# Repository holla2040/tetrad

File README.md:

# hexad
A 4-axis ESP32 GRBL board 

Board
    
    [Schematic](board/hexad-sch.pdf)

Requires
    [ESP32SSDP](https://github.com/luc-github/ESP32SSDP)

Compiling
    Select Board "ESP32 Dev Module"
    Flash Size "4MB (32Mb)"
    Partition Scheme "Minimal SPIFFS (1.9MB APP with OTA/190kB SPIFFS)"

    set options, like N_AXIS in config.h

----

Based on Dring's ESP32 GRBL port
 * [Grbl_ESP32 Development Board Version 3.1](http://www.buildlog.net/blog/2018/11/grbl_esp32-development-board-version-3-1/) 
 * [Source](https://github.com/bdring/Grbl_Esp32)
 * [Schematic](http://www.buildlog.net/blog/wp-content/uploads/2018/10/schm_esp32_cnc_test_v3p1.pdf)
 * [Wiki](https://github.com/bdring/Grbl_Esp32/wiki)

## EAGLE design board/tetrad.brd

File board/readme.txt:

This information, board files, assembly instructions and bill of
materials are company confidental.
Not for distribution.

board
    hexad

version
    v1.0

date
    191101

fudicials at
    x,y
    x,y

2 layer description
    2 layer board
        crc component cream
        plc component side silkscreen
        stc component side solder stop mask
        cmp component side copper
        sol solder side copper
        sts solder side solder stop mask
        pls solder side silkscreen
        crs solder cream

        drd drill data
        dri drill info
        gpi gerber info

2 layer stack up sequence
    top     x.cmp
    bottom  x.sol

contact info
    Craig Hollabaugh
    970 690 4911
    craig@hollabaugh.com

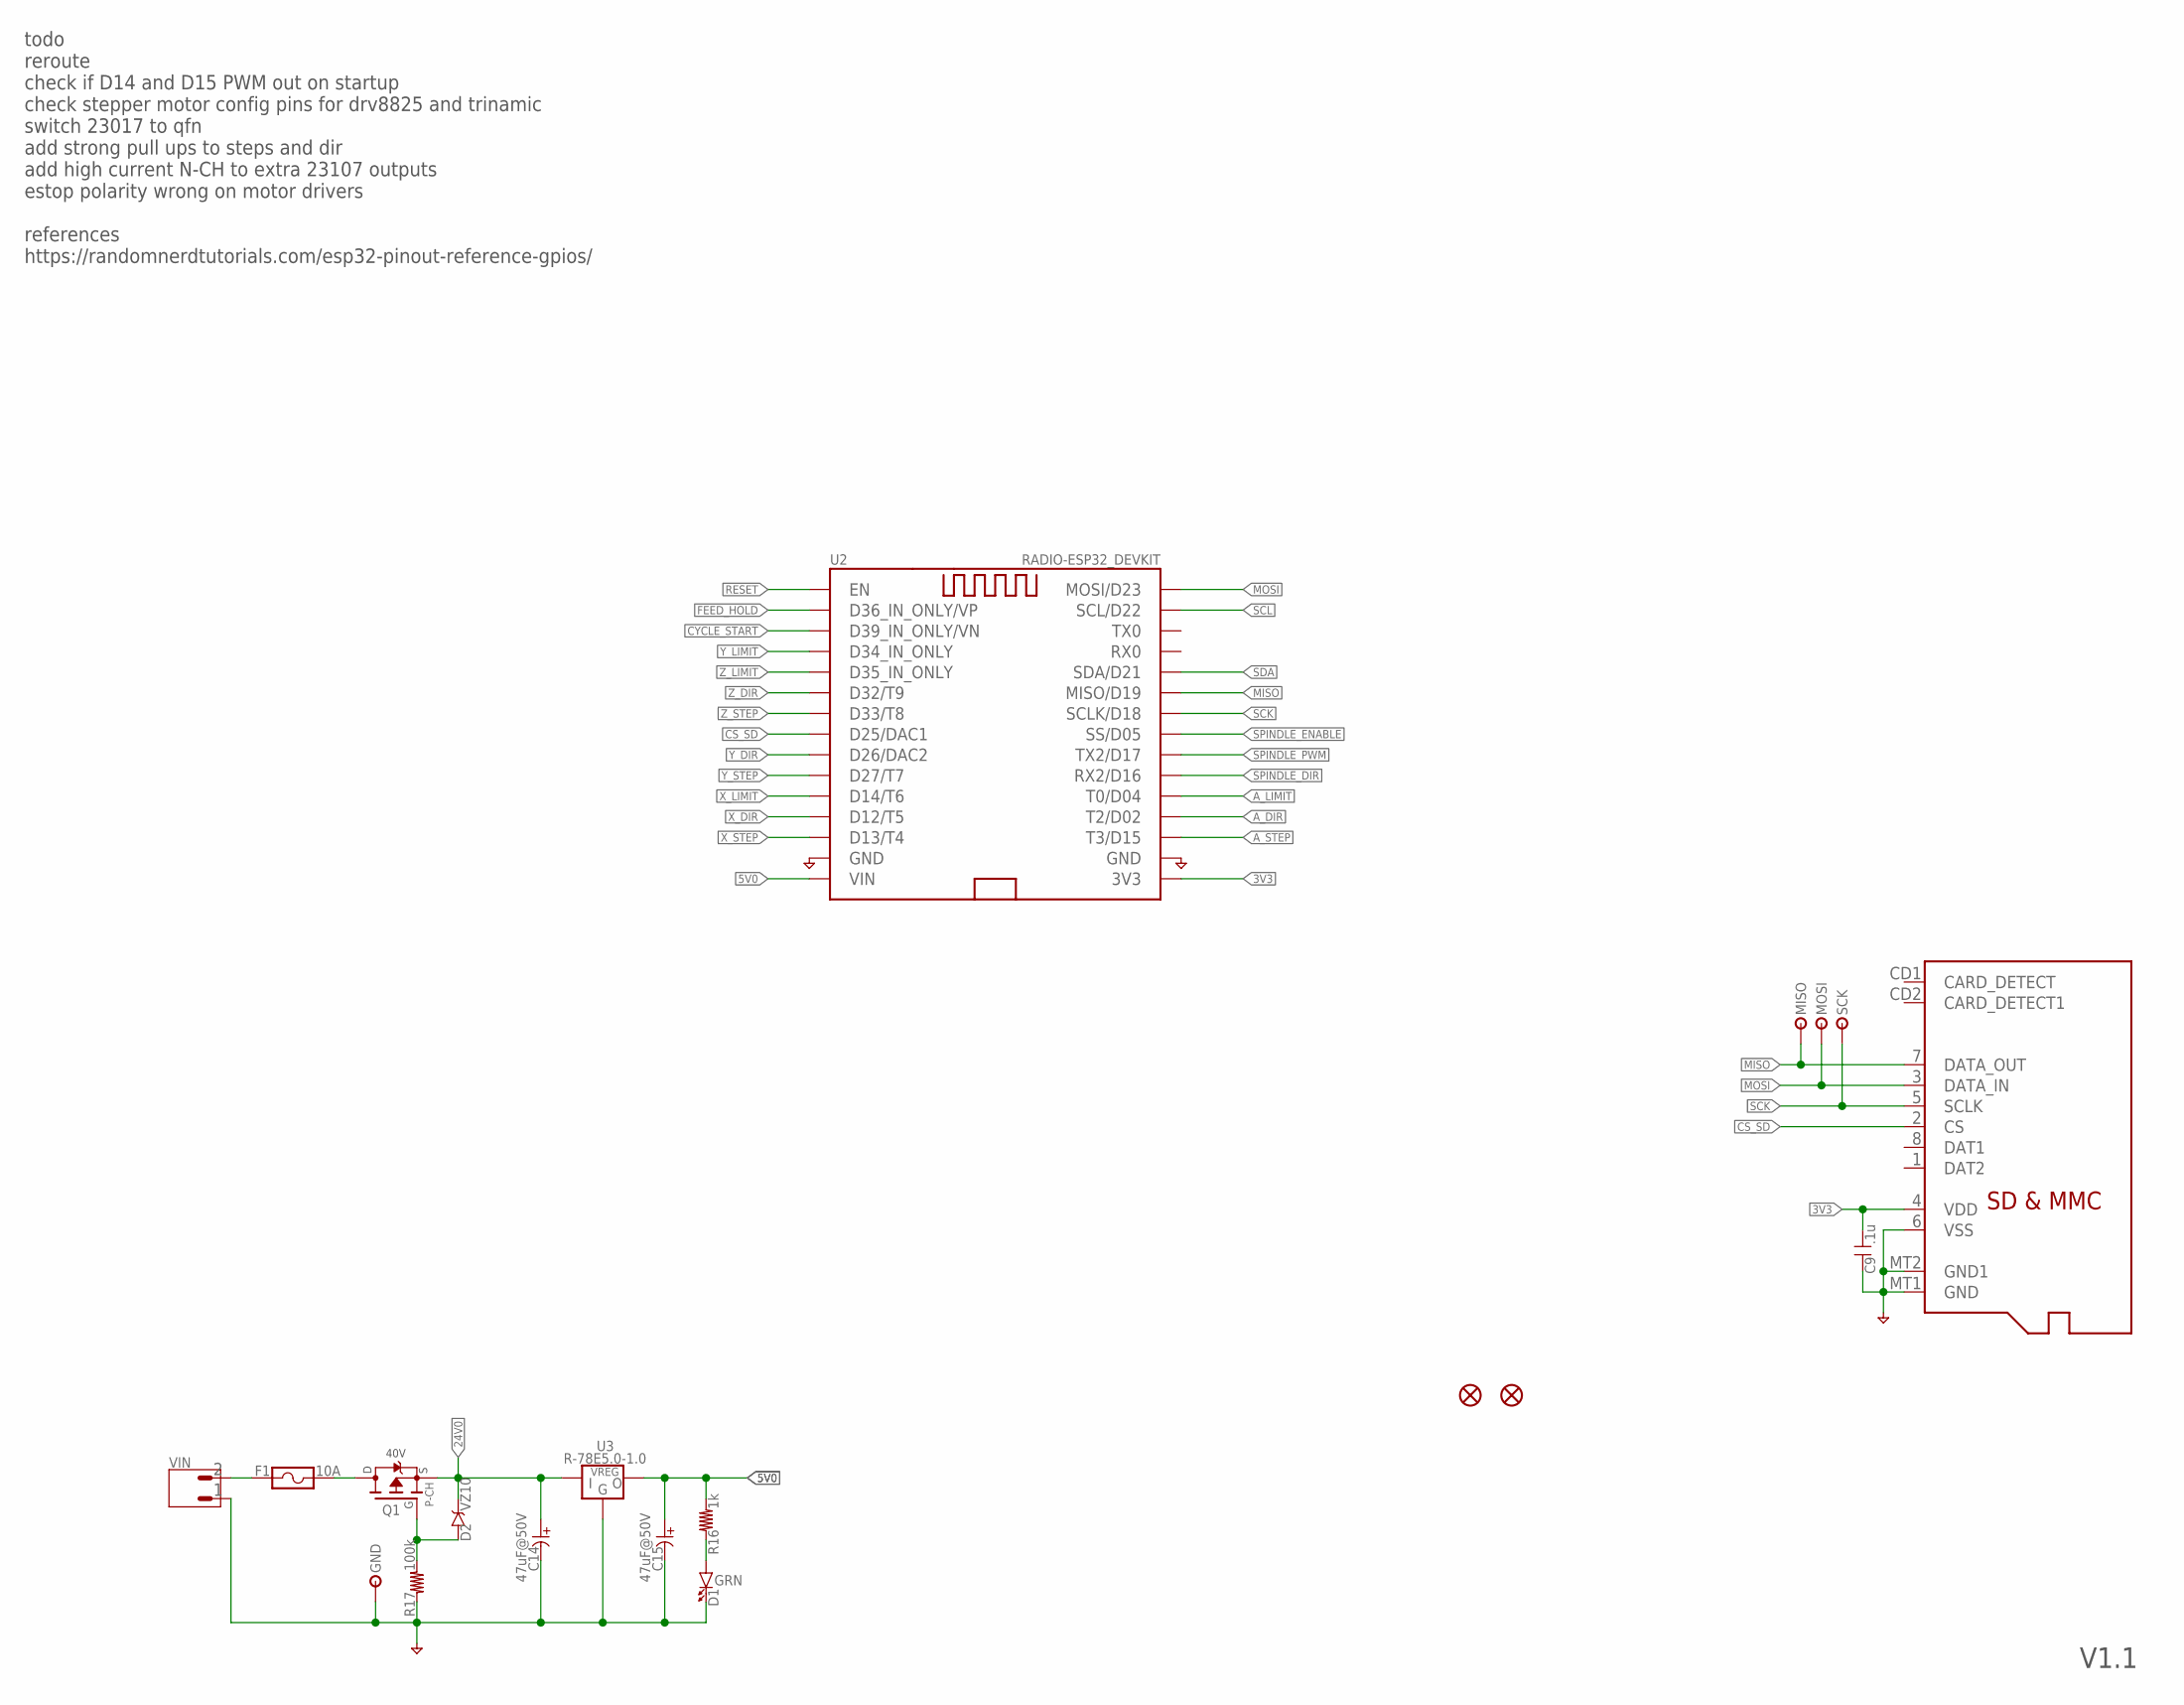
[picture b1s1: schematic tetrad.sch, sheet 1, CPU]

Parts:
C9: .1u; C-0603
C14, C15: 47uF@50V; C-E-6
D1: GRN; LED-0603
D2: VZ10; D-SOD323
F1: 10A; 3557-2
FID1, FID2: FIDUCIAL-MICRO
GND: TESTPOINTTHRU; TPTHRU
J1: CONN-MICROSD-2908-05WB-MG
MISO: TESTPOINTTHRU; TPTHRU
MOSI: TESTPOINTTHRU; TPTHRU
Q1: FET-PCH-TO252; TO252
R16: 1k; R-0603
R17: 100k; R-0603
SCK: TESTPOINTTHRU; TPTHRU
U2: RADIO-ESP32_DEVKIT; ESP32_DEVKIT
U3: R-78E5.0-1.0; VREG-SIP3
VIN: CONN-02-3.81MM-PLUGIN-SCREW; CONN-3.81MM-KF2EDG-2

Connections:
3V3: C9.1, J1.4 (VDD), U2.3V3; also elsewhere on the board
5V0: C15.+, R16.2, U2.VIN, U3.3 (VOUT); also elsewhere on the board
24V0: C14.+, D2.C, Q1.2 (S), U3.1 (VIN); also elsewhere on the board
A_DIR: U2.D2 (T2/D02); also elsewhere on the board
A_LIMIT: U2.D4 (T0/D04)
A_STEP: U2.D15 (T3/D15); also elsewhere on the board
CS_SD: J1.2 (CS), U2.D25 (D25/DAC1)
CYCLE_START: U2.VN (D39_IN_ONLY/VN); also elsewhere on the board
FEED_HOLD: U2.VP (D36_IN_ONLY/VP); also elsewhere on the board
GND: C9.2, C14.-, C15.-, D1.C, GND.1, J1.6 (VSS), J1.MT1 (GND), J1.MT2 (GND1), R17.1, U2.GND@1 (GND), U2.GND@2 (GND), U3.2 (GND), VIN.1; also elsewhere on the board
MISO: J1.7 (DATA_OUT), MISO.1, U2.D19 (MISO/D19); also elsewhere on the board
MOSI: J1.3 (DATA_IN), MOSI.1, U2.D23 (MOSI/D23); also elsewhere on the board
unnamed: F1.1@1, F1.1@2, VIN.2
unnamed: D2.A, Q1.1 (G), R17.2
unnamed: F1.2@1, F1.2@2, Q1.3 (D)
unnamed: D1.A, R16.1
RESET: U2.EN; also elsewhere on the board
SCK: J1.5 (SCLK), SCK.1, U2.D18 (SCLK/D18); also elsewhere on the board
SCL: U2.D22 (SCL/D22); also elsewhere on the board
SDA: U2.D21 (SDA/D21); also elsewhere on the board
SPINDLE_DIR: U2.RX2 (RX2/D16); also elsewhere on the board
SPINDLE_ENABLE: U2.D5 (SS/D05); also elsewhere on the board
SPINDLE_PWM: U2.TX2 (TX2/D17); also elsewhere on the board
X_DIR: U2.D12 (D12/T5); also elsewhere on the board
X_LIMIT: U2.D14 (D14/T6); also elsewhere on the board
X_STEP: U2.D13 (D13/T4); also elsewhere on the board
Y_DIR: U2.D26 (D26/DAC2); also elsewhere on the board
Y_LIMIT: U2.D34 (D34_IN_ONLY)
Y_STEP: U2.D27 (D27/T7); also elsewhere on the board
Z_DIR: U2.D32 (D32/T9); also elsewhere on the board
Z_LIMIT: U2.D35 (D35_IN_ONLY)
Z_STEP: U2.D33 (D33/T8); also elsewhere on the board

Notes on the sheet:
todo reroute check if D14 and D15 PWM out on startup check stepper motor config pins for drv8825 and trinamic switch 23017 to qfn add strong pull ups to steps and dir add high current N-CH to extra 23107 outputs estop polarity wrong on motor drivers references https://randomnerdtutorials.com/esp32-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
40V
V1.1

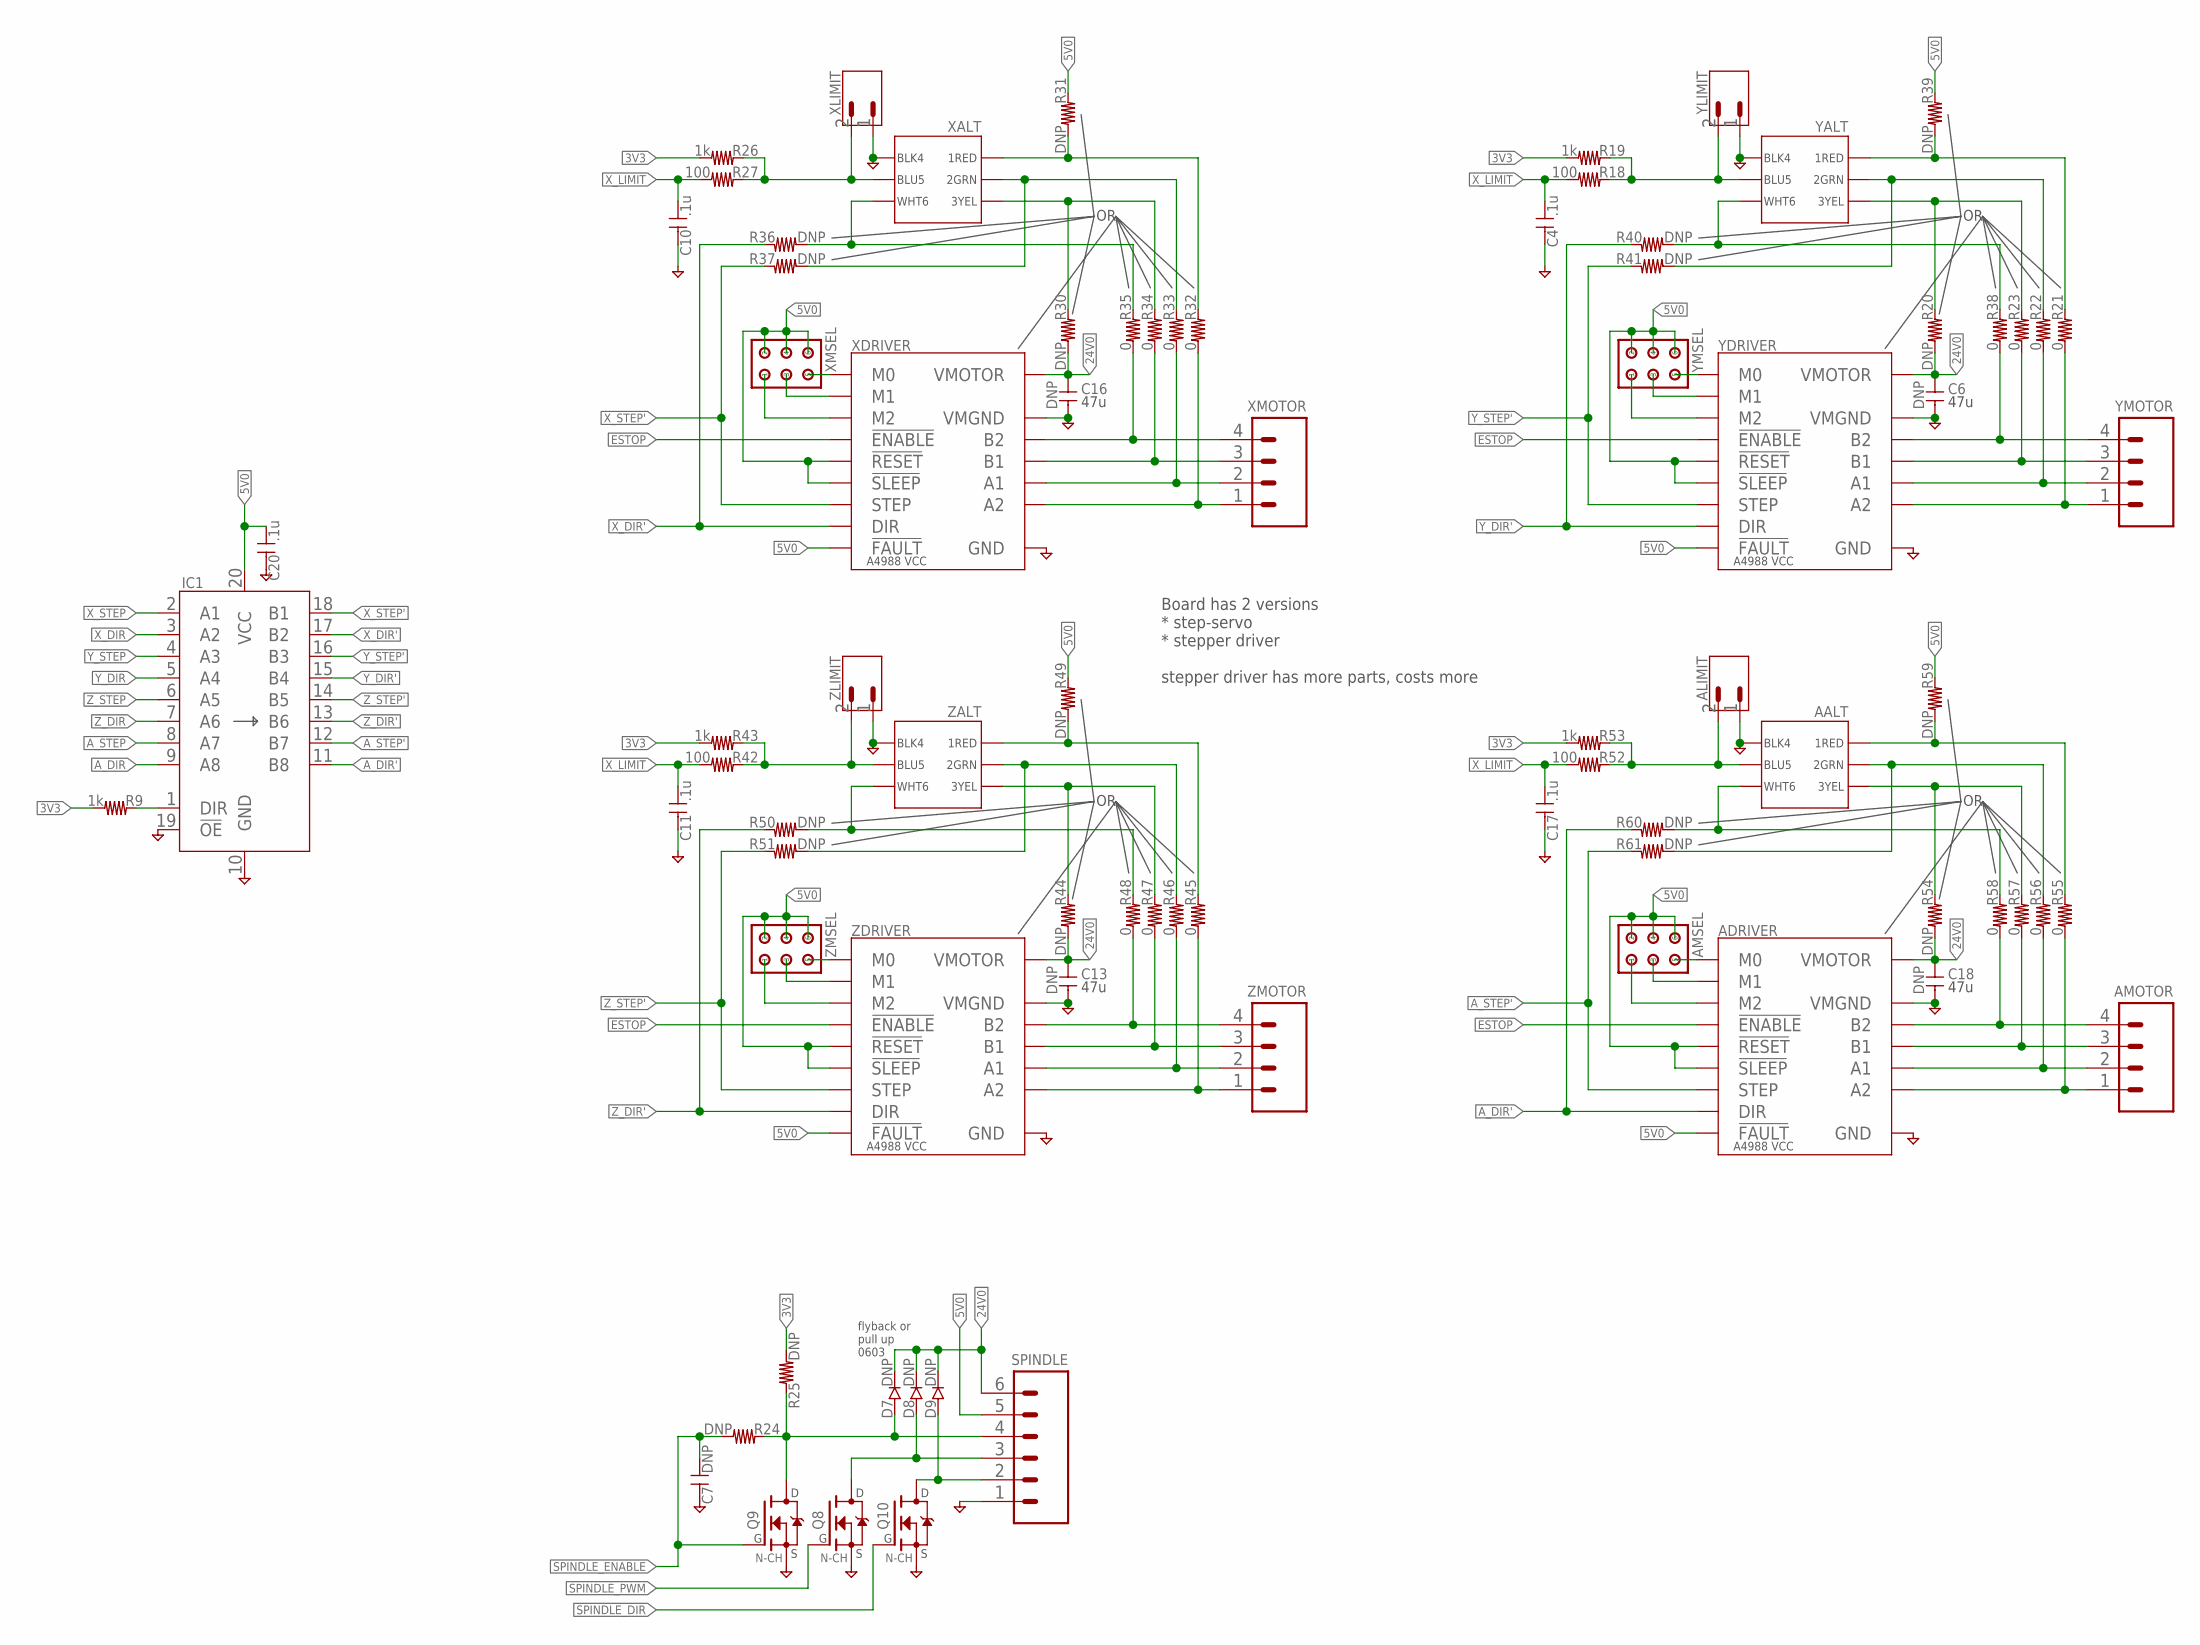
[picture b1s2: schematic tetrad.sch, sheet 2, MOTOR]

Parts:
AALT: CONN-03X2-MICROFIT-TH-SMD; MOLEX_430450614_430450615
ADRIVER: BOARD-DRV8825-CARRIER-TH-SMD; IC_DRV8825_CARRIER_TH_SMD
ALIMIT: CONN-02-.100-VERT-HEADER; CONN-.100-2
AMOTOR: CONN-04-.100-VERT-HEADER; CONN-.100-4
AMSEL: CONN-03X2-RH; AMPHENOL_95278-101A06LF
C4, C10, C11, C17, C20: .1u; C-0603
C6, C13, C16, C18: DNP; C-1206
C7: DNP; C-0603
D7, D8, D9: DNP; D-SOD523
IC1: 74LS245DW; SO20W
Q8, Q9, Q10: FET-NCH-SOT23; SOT23-3
R9, R19, R26, R43, R53: 1k; R-0603
R18, R27, R42, R52: 100; R-0603
R20, R24, R25, R30, R31, R36, R37, R39, R40, R41, R44, R49, R50, R51, R54, R59, R60, R61: DNP; R-0603
R21, R22, R23, R32, R33, R34, R35, R38, R45, R46, R47, R48, R55, R56, R57, R58: 0; R-0603
SPINDLE: CONN-06-.100-VERT-HEADER; CONN-.100-6
XALT: CONN-03X2-MICROFIT-TH-SMD; MOLEX_430450614_430450615
XDRIVER: BOARD-DRV8825-CARRIER-TH-SMD; IC_DRV8825_CARRIER_TH_SMD
XLIMIT: CONN-02-.100-VERT-HEADER; CONN-.100-2
XMOTOR: CONN-04-.100-VERT-HEADER; CONN-.100-4
XMSEL: CONN-03X2-RH; AMPHENOL_95278-101A06LF
YALT: CONN-03X2-MICROFIT-TH-SMD; MOLEX_430450614_430450615
YDRIVER: BOARD-DRV8825-CARRIER-TH-SMD; IC_DRV8825_CARRIER_TH_SMD
YLIMIT: CONN-02-.100-VERT-HEADER; CONN-.100-2
YMOTOR: CONN-04-.100-VERT-HEADER; CONN-.100-4
YMSEL: CONN-03X2-RH; AMPHENOL_95278-101A06LF
ZALT: CONN-03X2-MICROFIT-TH-SMD; MOLEX_430450614_430450615
ZDRIVER: BOARD-DRV8825-CARRIER-TH-SMD; IC_DRV8825_CARRIER_TH_SMD
ZLIMIT: CONN-02-.100-VERT-HEADER; CONN-.100-2
ZMOTOR: CONN-04-.100-VERT-HEADER; CONN-.100-4
ZMSEL: CONN-03X2-RH; AMPHENOL_95278-101A06LF

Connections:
3V3: R9.2, R19.2, R25.2, R26.2, R43.2, R53.2; also elsewhere on the board
5V0: ADRIVER.5 (!RESET), ADRIVER.5_ (!RESET), ADRIVER.6 (!SLEEP), ADRIVER.6_ (!SLEEP), ADRIVER.10 (!FAULT), ADRIVER.10_ (!FAULT), AMSEL.2, AMSEL.4, AMSEL.6, C20.1, IC1.20 (VCC), R31.1, R39.1, R49.1, R59.1, SPINDLE.5, XDRIVER.5 (!RESET), XDRIVER.5_ (!RESET), XDRIVER.6 (!SLEEP), XDRIVER.6_ (!SLEEP), XDRIVER.10 (!FAULT), XDRIVER.10_ (!FAULT), XMSEL.2, XMSEL.4, XMSEL.6, YDRIVER.5 (!RESET), YDRIVER.5_ (!RESET), YDRIVER.6 (!SLEEP), YDRIVER.6_ (!SLEEP), YDRIVER.10 (!FAULT), YDRIVER.10_ (!FAULT), YMSEL.2, YMSEL.4, YMSEL.6, ZDRIVER.5 (!RESET), ZDRIVER.5_ (!RESET), ZDRIVER.6 (!SLEEP), ZDRIVER.6_ (!SLEEP), ZDRIVER.10 (!FAULT), ZDRIVER.10_ (!FAULT), ZMSEL.2, ZMSEL.4, ZMSEL.6; also elsewhere on the board
24V0: ADRIVER.16 (VMOTOR), ADRIVER.16_ (VMOTOR), C6.1, C13.1, C16.1, C18.1, D7.C, D8.C, D9.C, R20.2, R30.2, R44.2, R54.2, SPINDLE.6, XDRIVER.16 (VMOTOR), XDRIVER.16_ (VMOTOR), YDRIVER.16 (VMOTOR), YDRIVER.16_ (VMOTOR), ZDRIVER.16 (VMOTOR), ZDRIVER.16_ (VMOTOR); also elsewhere on the board
A_DIR: IC1.9 (A8); also elsewhere on the board
A_DIR': ADRIVER.8 (DIR), ADRIVER.8_ (DIR), IC1.11 (B8), R60.1
A_STEP: IC1.8 (A7); also elsewhere on the board
A_STEP': ADRIVER.7 (STEP), ADRIVER.7_ (STEP), IC1.12 (B7), R61.1
ESTOP: ADRIVER.1 (!ENABLE), ADRIVER.1_ (!ENABLE), XDRIVER.1 (!ENABLE), XDRIVER.1_ (!ENABLE), YDRIVER.1 (!ENABLE), YDRIVER.1_ (!ENABLE), ZDRIVER.1 (!ENABLE), ZDRIVER.1_ (!ENABLE); also elsewhere on the board
GND: AALT.4, AALT.4_ (4), ADRIVER.9 (GND), ADRIVER.9_ (GND), ADRIVER.15 (VMGND), ADRIVER.15_ (VMGND), ALIMIT.1, C4.2, C6.2, C7.2, C10.2, C11.2, C13.2, C16.2, C17.2, C18.2, C20.2, IC1.10 (GND), IC1.19 (!OE), Q8.2 (S), Q9.2 (S), Q10.2 (S), SPINDLE.1, XALT.4, XALT.4_ (4), XDRIVER.9 (GND), XDRIVER.9_ (GND), XDRIVER.15 (VMGND), XDRIVER.15_ (VMGND), XLIMIT.1, YALT.4, YALT.4_ (4), YDRIVER.9 (GND), YDRIVER.9_ (GND), YDRIVER.15 (VMGND), YDRIVER.15_ (VMGND), YLIMIT.1, ZALT.4, ZALT.4_ (4), ZDRIVER.9 (GND), ZDRIVER.9_ (GND), ZDRIVER.15 (VMGND), ZDRIVER.15_ (VMGND), ZLIMIT.1; also elsewhere on the board
unnamed: R30.1, R34.1, XALT.3, XALT.3_ (3)
unnamed: IC1.1 (DIR), R9.1
unnamed: R31.2, R32.1, XALT.1, XALT.1_ (1)
unnamed: R21.2, YDRIVER.11 (A2), YDRIVER.11_ (A2), YMOTOR.1
unnamed: YDRIVER.2 (M0), YDRIVER.2_ (M0), YMSEL.5
unnamed: YDRIVER.3 (M1), YDRIVER.3_ (M1), YMSEL.3
unnamed: YDRIVER.4 (M2), YDRIVER.4_ (M2), YMSEL.1
unnamed: R22.2, YDRIVER.12 (A1), YDRIVER.12_ (A1), YMOTOR.2
unnamed: R23.2, YDRIVER.13 (B1), YDRIVER.13_ (B1), YMOTOR.3
unnamed: D7.A, Q9.3 (D), R24.1, R25.1, SPINDLE.4
unnamed: D9.A, Q10.3 (D), SPINDLE.2
unnamed: R38.2, YDRIVER.14 (B2), YDRIVER.14_ (B2), YMOTOR.4
unnamed: R32.2, XDRIVER.11 (A2), XDRIVER.11_ (A2), XMOTOR.1
unnamed: R18.1, R19.1, YALT.5, YALT.5_ (5), YLIMIT.2
unnamed: XDRIVER.2 (M0), XDRIVER.2_ (M0), XMSEL.5
unnamed: XDRIVER.3 (M1), XDRIVER.3_ (M1), XMSEL.3
unnamed: XDRIVER.4 (M2), XDRIVER.4_ (M2), XMSEL.1
unnamed: R38.1, R40.2, YALT.6, YALT.6_ (6)
unnamed: R21.1, R39.2, YALT.1, YALT.1_ (1)
unnamed: R20.1, R23.1, YALT.3, YALT.3_ (3)
unnamed: R45.2, ZDRIVER.11 (A2), ZDRIVER.11_ (A2), ZMOTOR.1
unnamed: ZDRIVER.2 (M0), ZDRIVER.2_ (M0), ZMSEL.5
unnamed: ZDRIVER.3 (M1), ZDRIVER.3_ (M1), ZMSEL.3
unnamed: ZDRIVER.4 (M2), ZDRIVER.4_ (M2), ZMSEL.1
unnamed: R46.2, ZDRIVER.12 (A1), ZDRIVER.12_ (A1), ZMOTOR.2
unnamed: R47.2, ZDRIVER.13 (B1), ZDRIVER.13_ (B1), ZMOTOR.3
unnamed: R48.2, ZDRIVER.14 (B2), ZDRIVER.14_ (B2), ZMOTOR.4
unnamed: R42.1, R43.1, ZALT.5, ZALT.5_ (5), ZLIMIT.2
unnamed: R48.1, R50.2, ZALT.6, ZALT.6_ (6)
unnamed: R45.1, R49.2, ZALT.1, ZALT.1_ (1)
unnamed: R44.1, R47.1, ZALT.3, ZALT.3_ (3)
unnamed: ADRIVER.11 (A2), ADRIVER.11_ (A2), AMOTOR.1, R55.2
unnamed: R35.2, XDRIVER.14 (B2), XDRIVER.14_ (B2), XMOTOR.4
unnamed: R26.1, R27.1, XALT.5, XALT.5_ (5), XLIMIT.2
unnamed: ADRIVER.2 (M0), ADRIVER.2_ (M0), AMSEL.5
unnamed: R35.1, R36.2, XALT.6, XALT.6_ (6)
unnamed: ADRIVER.3 (M1), ADRIVER.3_ (M1), AMSEL.3
unnamed: R33.2, XDRIVER.12 (A1), XDRIVER.12_ (A1), XMOTOR.2
unnamed: R34.2, XDRIVER.13 (B1), XDRIVER.13_ (B1), XMOTOR.3
unnamed: ADRIVER.4 (M2), ADRIVER.4_ (M2), AMSEL.1
unnamed: ADRIVER.12 (A1), ADRIVER.12_ (A1), AMOTOR.2, R56.2
unnamed: ADRIVER.13 (B1), ADRIVER.13_ (B1), AMOTOR.3, R57.2
unnamed: ADRIVER.14 (B2), ADRIVER.14_ (B2), AMOTOR.4, R58.2
unnamed: AALT.5, AALT.5_ (5), ALIMIT.2, R52.1, R53.1
unnamed: AALT.6, AALT.6_ (6), R58.1, R60.2
unnamed: AALT.1, AALT.1_ (1), R55.1, R59.2
unnamed: AALT.3, AALT.3_ (3), R54.1, R57.1
SPINDLE_DIR: Q10.1 (G); also elsewhere on the board
SPINDLE_ENABLE: C7.1, Q9.1 (G), R24.2; also elsewhere on the board
SPINDLE_PWM: Q8.1 (G); also elsewhere on the board
X_DIR: IC1.3 (A2); also elsewhere on the board
X_DIR': IC1.17 (B2), R36.1, XDRIVER.8 (DIR), XDRIVER.8_ (DIR)
X_LIMIT: C4.1, C10.1, C11.1, C17.1, R18.2, R27.2, R42.2, R52.2; also elsewhere on the board
X_STEP: IC1.2 (A1); also elsewhere on the board
X_STEP': IC1.18 (B1), R22.1, R33.1, R37.1, R37.2, R41.2, R46.1, R51.2, XALT.2, XALT.2_ (2), XDRIVER.7 (STEP), XDRIVER.7_ (STEP), YALT.2, YALT.2_ (2), ZALT.2, ZALT.2_ (2)
X_STEP'1: AALT.2, AALT.2_ (2), R56.1, R61.2
X_STEP_5V4: D8.A, Q8.3 (D), SPINDLE.3
Y_DIR: IC1.5 (A4); also elsewhere on the board
Y_DIR': IC1.15 (B4), R40.1, YDRIVER.8 (DIR), YDRIVER.8_ (DIR)
Y_STEP: IC1.4 (A3); also elsewhere on the board
Y_STEP': IC1.16 (B3), R41.1, YDRIVER.7 (STEP), YDRIVER.7_ (STEP)
Z_DIR: IC1.7 (A6); also elsewhere on the board
Z_DIR': IC1.13 (B6), R50.1, ZDRIVER.8 (DIR), ZDRIVER.8_ (DIR)
Z_STEP: IC1.6 (A5); also elsewhere on the board
Z_STEP': IC1.14 (B5), R51.1, ZDRIVER.7 (STEP), ZDRIVER.7_ (STEP)

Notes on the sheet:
47u
flyback or pull up 0603
Board has 2 versions * step-servo * stepper driver stepper driver has more parts, costs more

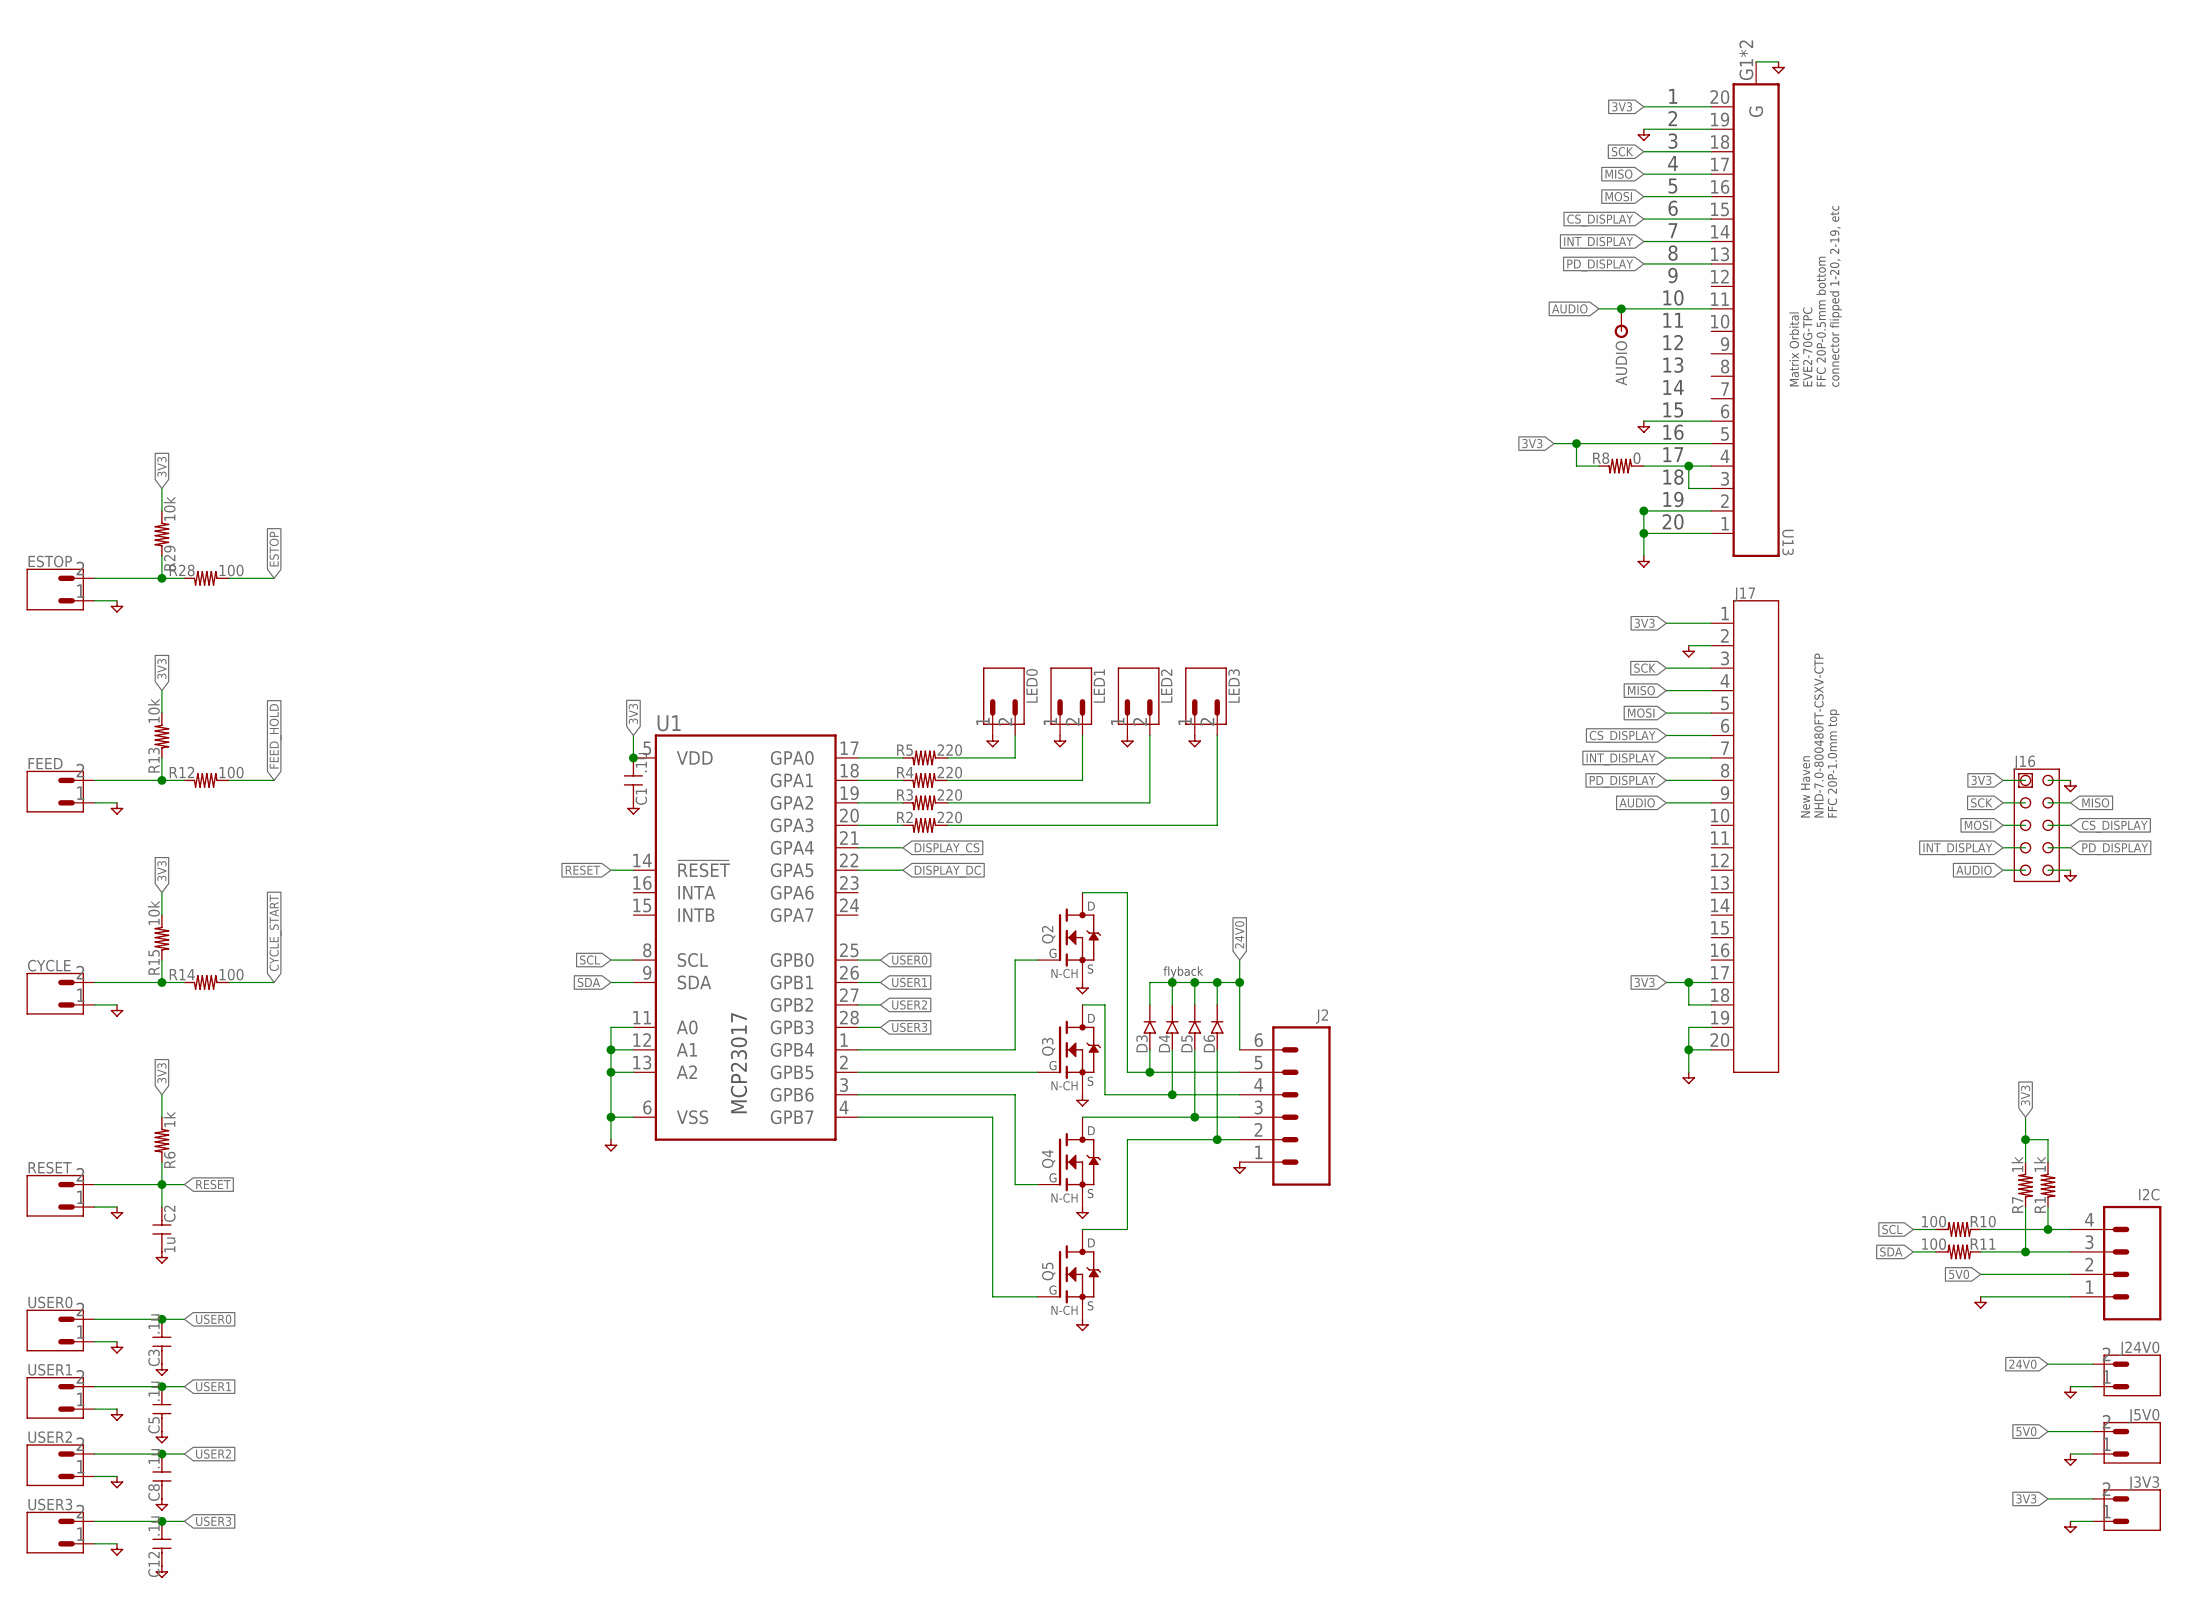
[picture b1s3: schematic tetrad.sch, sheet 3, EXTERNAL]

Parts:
AUDIO: TESTPOINTTHRU; TPTHRU
C1, C3, C5, C8, C12: .1u; C-0603
C2: 1u; C-0603
CYCLE: CONN-02-.100-VERT-HEADER; CONN-.100-2
D3, D4, D5, D6: DIODE-0603-SOD523; D-SOD523
ESTOP: CONN-02-.100-VERT-HEADER; CONN-.100-2
FEED: CONN-02-.100-VERT-HEADER; CONN-.100-2
I2C: CONN-04-.100-VERT-HEADER; CONN-.100-4
J2: CONN-06-3.81MM-PLUGIN-SCREW; CONN-3.81MM-KF2EDG-6
J3V3, J5V0, J24V0: CONN-02-.100-VERT-HEADER; CONN-.100-2
J16: CONN-05X2-SHD; 2X5-SHROUDED
J17: CONN-20-2-84952-0; CON20_SMT-RA_FCC-FPC2
LED0, LED1, LED2, LED3: CONN-02-.100-VERT-HEADER; CONN-.100-2
Q2, Q3, Q4, Q5: FET-NCH-TO252; TO252
R1, R6, R7: 1k; R-0603
R2, R3, R4, R5: 220; R-0603
R8: 0; R-0603
R10, R11, R12, R14, R28: 100; R-0603
R13, R15, R29: 10k; R-0603
RESET: CONN-02-.100-VERT-HEADER; CONN-.100-2
U1: IO-MCP23017ML; QFN28-ML_6X6MM
U13: CONN-20-FPC-0.50MM-10051922-2010ELF; FCI_10051922-2010ELF
USER0, USER1, USER2, USER3: CONN-02-.100-VERT-HEADER; CONN-.100-2

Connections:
3V3: C1.1, J3V3.2, J16.1, J17.1, J17.17, J17.18, R1.2, R6.2, R7.2, R8.1, R13.2, R15.2, R29.2, U1.5 (VDD), U13.5, U13.20; also elsewhere on the board
5V0: I2C.2, J5V0.2; also elsewhere on the board
24V0: D3.C, D4.C, D5.C, D6.C, J2.6, J24V0.2; also elsewhere on the board
AUDIO: AUDIO.1, J16.9, J17.9, U13.11
CS_DISPLAY: J16.6, J17.6, U13.15
CYCLE_START: R14.2; also elsewhere on the board
DISPLAY_CS: U1.21 (GPA4)
DISPLAY_DC: U1.22 (GPA5)
ESTOP: ESTOP.2, R28.1, R29.1; also elsewhere on the board
FEED_HOLD: R12.2; also elsewhere on the board
GND: C1.2, C2.1, C3.2, C5.2, C8.2, C12.2, CYCLE.1, ESTOP.1, FEED.1, I2C.1, J2.1, J3V3.1, J5V0.1, J16.2, J16.10, J17.2, J17.19, J17.20, J24V0.1, LED0.1, LED1.1, LED2.1, LED3.1, Q2.2 (S), Q3.2 (S), Q4.2 (S), Q5.2 (S), RESET.1, U1.6 (VSS), U1.11 (A0), U1.12 (A1), U1.13 (A2), U13.1, U13.2, U13.6, U13.19, U13.G1 (G), U13.G2 (G), USER0.1, USER1.1, USER2.1, USER3.1; also elsewhere on the board
INT_DISPLAY: J16.7, J17.7, U13.14
MISO: J16.4, J17.4, U13.17; also elsewhere on the board
MOSI: J16.5, J17.5, U13.16; also elsewhere on the board
unnamed: R5.1, U1.17 (GPA0)
unnamed: R4.1, U1.18 (GPA1)
unnamed: FEED.2, R12.1, R13.1
unnamed: CYCLE.2, R14.1, R15.1
unnamed: I2C.4, R1.1, R10.1
unnamed: I2C.3, R7.1, R11.1
unnamed: D6.A, J2.2, Q5.3 (D)
unnamed: R3.1, U1.19 (GPA2)
unnamed: R2.1, U1.20 (GPA3)
unnamed: LED3.2, R2.2
unnamed: LED2.2, R3.2
unnamed: LED1.2, R4.2
unnamed: LED0.2, R5.2
unnamed: D5.A, J2.3, Q4.3 (D)
unnamed: D4.A, J2.4, Q3.3 (D)
unnamed: D3.A, J2.5, Q2.3 (D)
unnamed: Q2.1 (G), U1.1 (GPB4)
unnamed: Q3.1 (G), U1.2 (GPB5)
unnamed: Q4.1 (G), U1.3 (GPB6)
unnamed: Q5.1 (G), U1.4 (GPB7)
unnamed: R8.2, U13.3, U13.4
PD_DISPLAY: J16.8, J17.8, U13.13
RESET: C2.2, R6.1, RESET.2, U1.14 (!RESET); also elsewhere on the board
SCK: J16.3, J17.3, U13.18; also elsewhere on the board
SCL: R10.2, U1.8 (SCL); also elsewhere on the board
SDA: R11.2, U1.9 (SDA); also elsewhere on the board
USER0: C3.1, U1.25 (GPB0), USER0.2
USER1: C5.1, U1.26 (GPB1), USER1.2
USER2: C8.1, U1.27 (GPB2), USER2.2
USER3: C12.1, U1.28 (GPB3), USER3.2

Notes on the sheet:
Matrix Orbital EVE2-70G-TPC FFC 20P-0.5mm bottom connector flipped 1-20, 2-19, etc
New Haven NHD-7.0-800480FT-CSXV-CTP FFC 20P-1.0mm top
1 2 3 4 5 6 7 8 9 10 11 12 13 14 15 16 17 18 19 20
flyback

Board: 2 copper layers, 152 parts (0 on the bottom side), 116 nets, no tracks yet.
